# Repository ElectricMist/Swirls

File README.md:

PCBs and Front panels Available at Pusherman at a fair price :
https://pushermanproductions.com/product/swirls-lamb-8hp-tides-sheep-black-fr4-reversible-panel-pcb-set/

Swirls is a 8HP version of Mutable Instruments Tides

- PCB v1.0 is tested and working
  known issues :
  side holes for the trimmers are too small,
  Silkscreen Mistake (C26 & R27 are flipped)
  
- PCB V1.1 
  the errors of v1.0 are fixed
  
The front panel is double Side
  - One side for Swirls (running the Tides firmware)
  - One side for Lamb (running the Sheep firmware)

Please if you are planning to sell some pcbs and panels, contact me first.

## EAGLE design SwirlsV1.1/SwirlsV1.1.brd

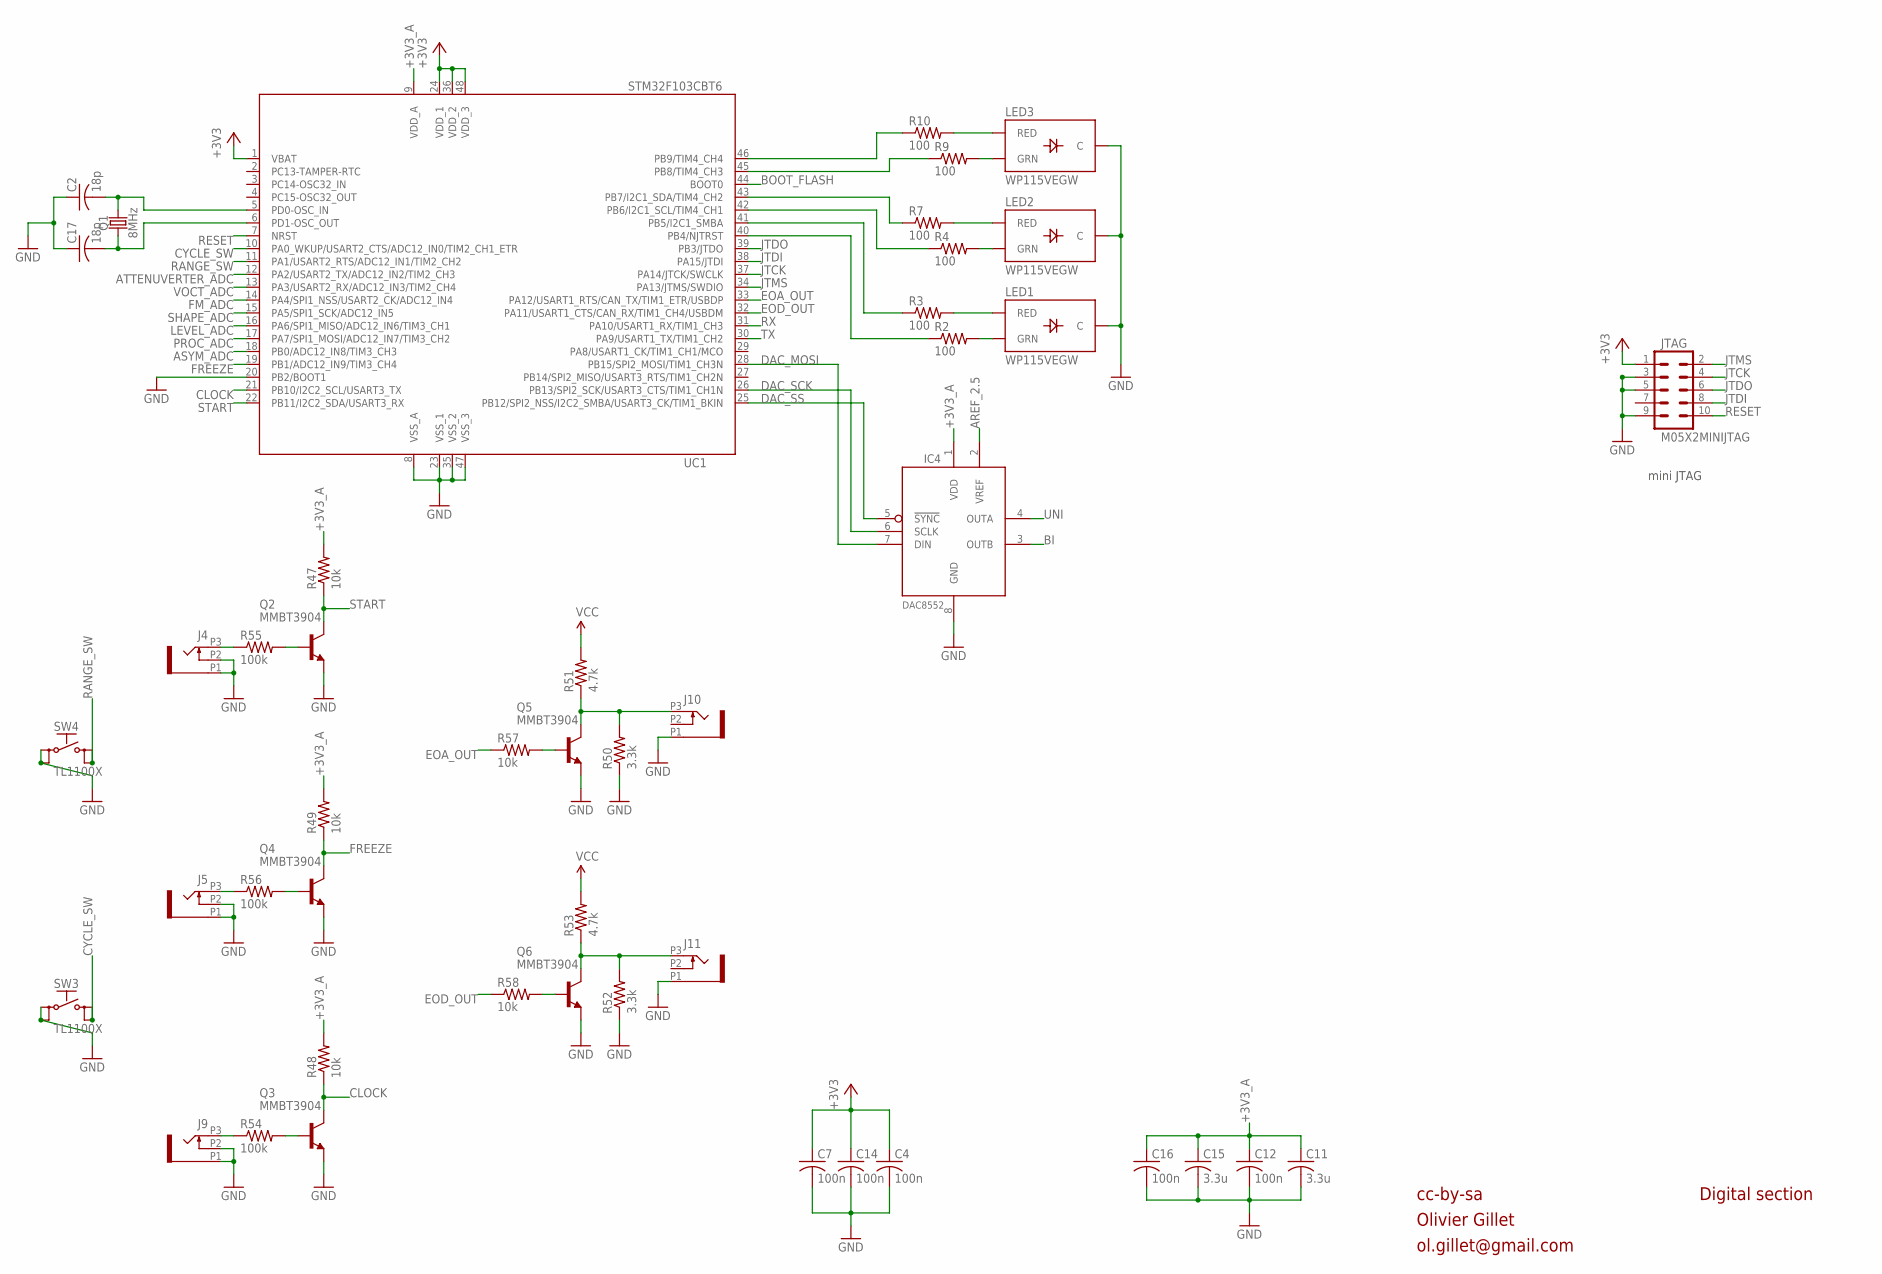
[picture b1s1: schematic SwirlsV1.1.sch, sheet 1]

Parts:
C2, C17: 18p; C0603
C4, C7, C12, C14, C16: 100n; C0603
C11, C15: 3.3u; C0603
IC4: DAC8552; MSOP-8
J4, J5, J9, J10, J11: PJ301_GUI6; OG-PJ301_VARIATIONS_WQP_PJ_301M6
JTAG: M05X2MINIJTAG; 2X5-1.27
LED1, LED2, LED3: WP115VEGW; LED-BICOLOR-THROUGHHOLE
Q1: 8MHz; HC49UP
Q2, Q3, Q4, Q5, Q6: MMBT3904; SOT23-BEC
R2, R3, R4, R7, R9, R10: 100; R0603
R47, R48, R49, R57, R58: 10k; R0603
R50, R52: 3.3k; R0603
R51, R53: 4.7k; R0603
R54, R55, R56: 100k; R0603
SW3, SW4: TL1100X
UC1: STM32F103CBT6; LQFP48

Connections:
+3V3: C4.1, C7.1, C14.1, JTAG.1, UC1.1 (VBAT), UC1.24 (VDD_1), UC1.36 (VDD_2), UC1.48 (VDD_3); also elsewhere on the board
+3V3_A: C11.1, C12.1, C15.1, C16.1, IC4.1 (VDD), R47.2, R48.2, R49.2, UC1.9 (VDD_A); also elsewhere on the board
AREF_2.5: IC4.2 (VREF); also elsewhere on the board
ASYM_ADC: UC1.18 (PB0/ADC12_IN8/TIM3_CH3); also elsewhere on the board
ATTENUVERTER_ADC: UC1.12 (PA2/USART2_TX/ADC12_IN2/TIM2_CH3); also elsewhere on the board
BI: IC4.3 (OUTB); also elsewhere on the board
BOOT_FLASH: UC1.44 (BOOT0)
CLOCK: Q3.C, R48.1, UC1.21 (PB10/I2C2_SCL/USART3_TX)
CYCLE_SW: SW3.3 (S), SW3.4 (S1), UC1.10 (PA0_WKUP/USART2_CTS/ADC12_IN0/TIM2_CH1_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)
DAC_MOSI: IC4.7 (DIN), UC1.28 (PB15/SPI2_MOSI/TIM1_CH3N)
DAC_SCK: IC4.6 (SCLK), UC1.26 (PB13/SPI2_SCK/USART3_CTS/TIM1_CH1N)
DAC_SS: IC4.5 (!SYNC), UC1.25 (PB12/SPI2_NSS/I2C2_SMBA/USART3_CK/TIM1_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)
EOA_OUT: R57.1, UC1.33 (PA12/USART1_RTS/CAN_TX/TIM1_ETR/USBDP)
EOD_OUT: R58.1, UC1.32 (PA11/USART1_CTS/CAN_RX/TIM1_CH4/USBDM)
FM_ADC: UC1.14 (PA4/SPI1_NSS/USART2_CK/ADC12_IN4); also elsewhere on the board
FREEZE: Q4.C, R49.1, UC1.19 (PB1/ADC12_IN9/TIM3_CH4)
GND: C2.1, C4.2, C7.2, C11.2, C12.2, C14.2, C15.2, C16.2, C17.1, IC4.8 (GND), J4.P1 (1), J4.P2 (2), J5.P1 (1), J5.P2 (2), J9.P1 (1), J9.P2 (2), J10.P1 (1), J11.P1 (1), JTAG.3, JTAG.5, JTAG.9, LED1.2 (C), LED2.2 (C), LED3.2 (C), Q2.E, Q3.E, Q4.E, Q5.E, Q6.E, R50.1, R52.1, SW3.1, SW3.2 (P1), SW4.1, SW4.2 (P1), UC1.8 (VSS_A), UC1.20 (PB2/BOOT1), UC1.23 (VSS_1), UC1.35 (VSS_2), UC1.47 (VSS_3); also elsewhere on the board
JTCK: JTAG.4, UC1.37 (PA14/JTCK/SWCLK)
JTDI: JTAG.8, UC1.38 (PA15/JTDI)
JTDO: JTAG.6, UC1.39 (PB3/JTDO)
JTMS: JTAG.2, UC1.34 (PA13/JTMS/SWDIO)
LEVEL_ADC: UC1.16 (PA6/SPI1_MISO/ADC12_IN6/TIM3_CH1); also elsewhere on the board
unnamed: C2.2, Q1.2, UC1.5 (PD0-OSC_IN)
unnamed: C17.2, Q1.1, UC1.6 (PD1-OSC_OUT)
unnamed: J5.P3 (3), R56.1
unnamed: Q4.B, R56.2
unnamed: J9.P3 (3), R54.1
unnamed: Q3.B, R54.2
unnamed: Q6.B, R58.2
unnamed: J11.P3 (3), Q6.C, R52.2, R53.1
unnamed: LED3.3 (RED), R10.2
unnamed: LED3.1 (GRN), R9.2
unnamed: LED2.3 (RED), R7.2
unnamed: LED2.1 (GRN), R4.2
unnamed: LED1.3 (RED), R3.2
unnamed: LED1.1 (GRN), R2.2
unnamed: R10.1, UC1.46 (PB9/TIM4_CH4)
unnamed: R9.1, UC1.45 (PB8/TIM4_CH3)
unnamed: R7.1, UC1.43 (PB7/I2C1_SDA/TIM4_CH2)
unnamed: R4.1, UC1.42 (PB6/I2C1_SCL/TIM4_CH1)
unnamed: R3.1, UC1.41 (PB5/I2C1_SMBA)
unnamed: R2.1, UC1.40 (PB4/NJTRST)
unnamed: J10.P3 (3), Q5.C, R50.2, R51.1
unnamed: Q5.B, R57.2
unnamed: J4.P3 (3), R55.1
unnamed: Q2.B, R55.2
PROC_ADC: UC1.17 (PA7/SPI1_MOSI/ADC12_IN7/TIM3_CH2); also elsewhere on the board
RANGE_SW: SW4.3 (S), SW4.4 (S1), UC1.11 (PA1/USART2_RTS/ADC12_IN1/TIM2_CH2)
RESET: JTAG.10, UC1.7 (NRST)
RX: UC1.31 (PA10/USART1_RX/TIM1_CH3)
SHAPE_ADC: UC1.15 (PA5/SPI1_SCK/ADC12_IN5); also elsewhere on the board
START: Q2.C, R47.1, UC1.22 (PB11/I2C2_SDA/USART3_RX)
TX: UC1.30 (PA9/USART1_TX/TIM1_CH2)
UNI: IC4.4 (OUTA); also elsewhere on the board
VCC: R51.2, R53.2; also elsewhere on the board
VOCT_ADC: UC1.13 (PA3/USART2_RX/ADC12_IN3/TIM2_CH4); also elsewhere on the board

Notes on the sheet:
cc-by-sa
Olivier Gillet
ol.gillet@gmail.com
Digital section
mini JTAG

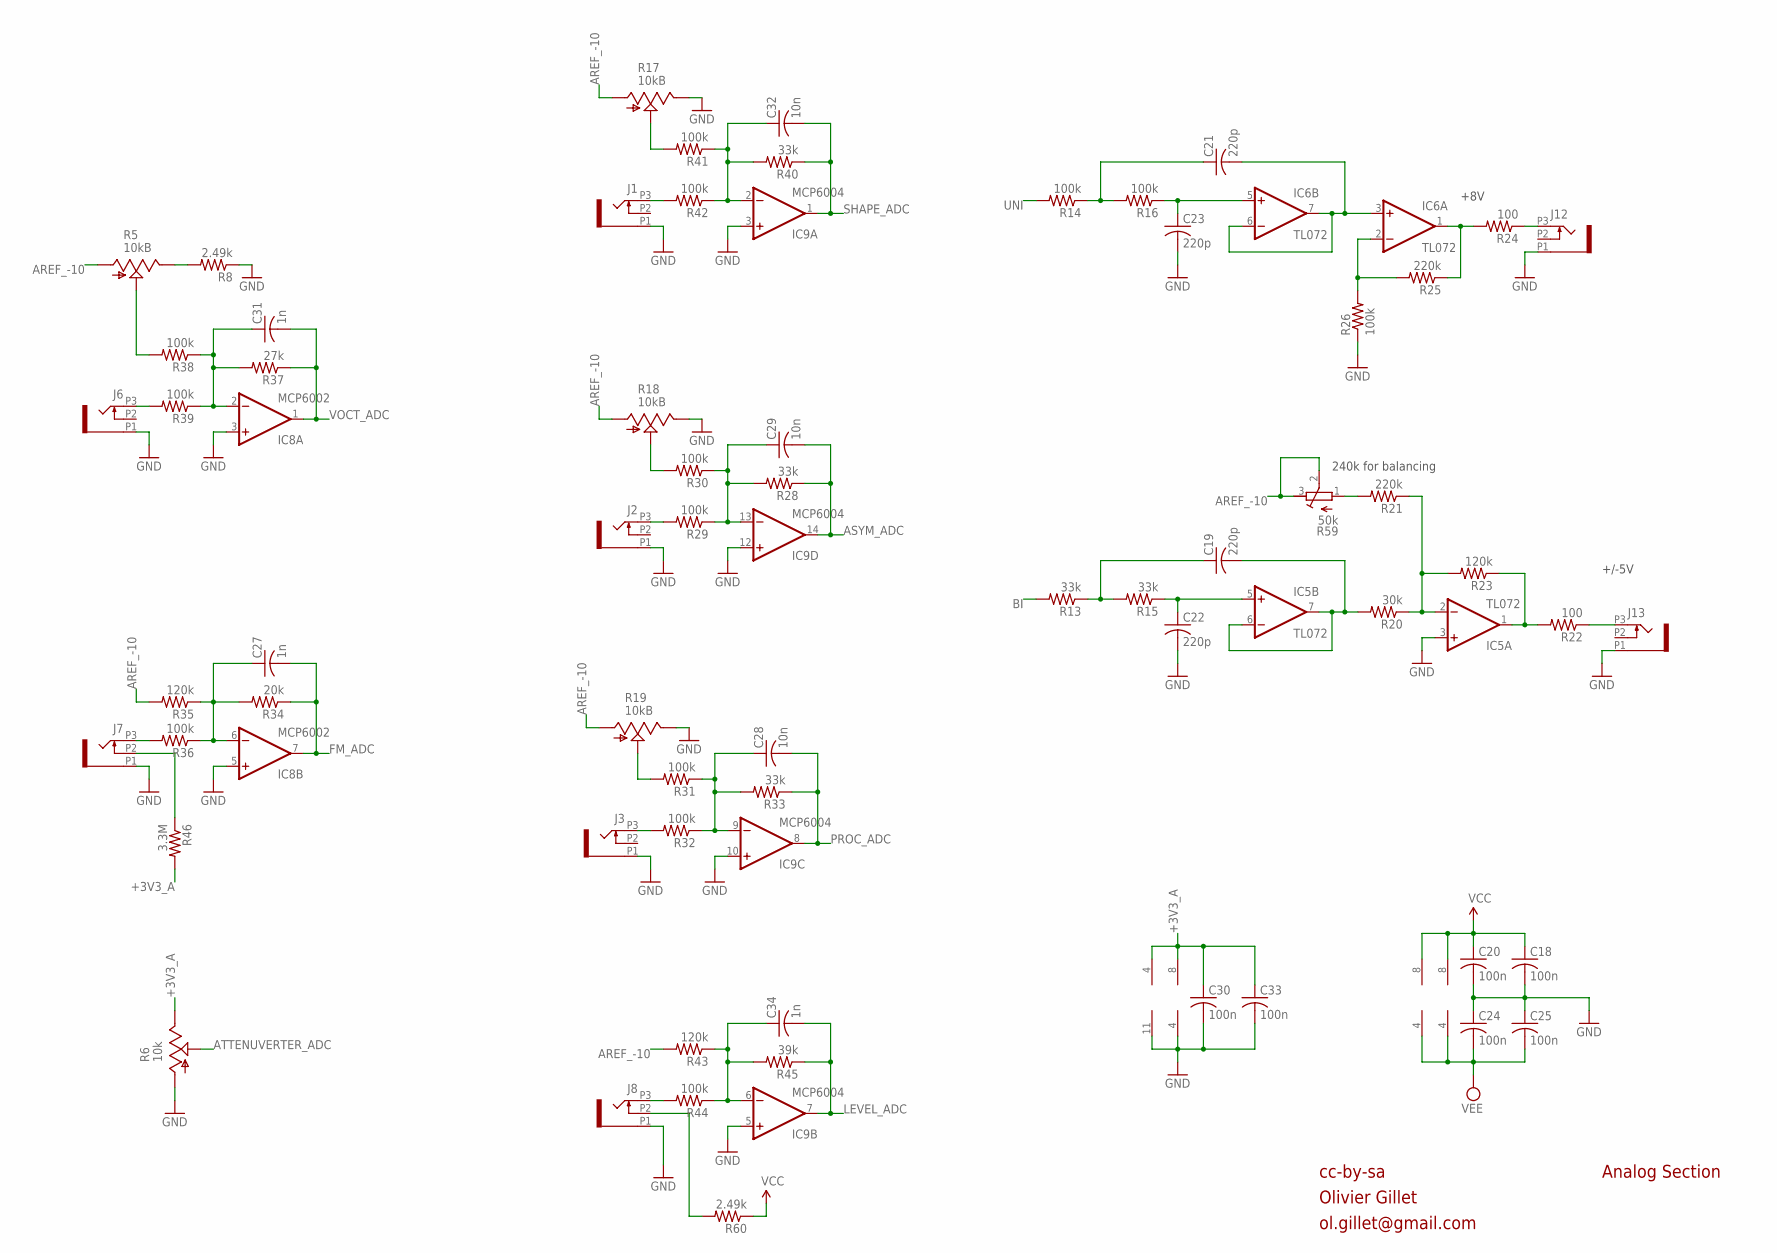
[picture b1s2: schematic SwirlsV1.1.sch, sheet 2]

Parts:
C18, C20, C24, C25, C30, C33: 100n; C0603
C19, C21, C22, C23: 220p; C0603
C27, C31, C34: 1n; C0603
C28, C29, C32: 10n; C0603
IC5, IC6: TL072; TSSOP-8
IC8: MCP6002; SO08
IC9: MCP6004; TSSOP14
J1, J2, J3, J6, J7, J8, J12, J13: PJ301_GUI6; OG-PJ301_VARIATIONS_WQP_PJ_301M6
R5: 10kB; ALPS_POT_VERTICAL_PS
R6: 10k; TALLTRIMMER
R8: 2.49k; R0603
R13, R15, R28, R33, R40: 33k; R0603
R14, R16, R26, R29, R30, R31, R32, R36, R38, R39, R41, R42, R44: 100k; R0603
R17, R18, R19: 10kB; TALLTRIMMER
R20: 30k; R0603
R21, R25: 220k; R0603
R22, R24: 100; R0603
R23, R35, R43: 120k; R0603
R34: 20k; R0603
R37: 27k; R0603
R45: 39k; R0603
R46: 3.3M; R0603
R59: 50k; RTRIM3296W
R60: 2.49k; R0805

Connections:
+3V3_A: C30.1, C33.1, IC8.8 (V+), IC9.4 (V+), R6.P$1 (E), R46.2; also elsewhere on the board
AREF_-10: R5.P$3 (A), R17.P$3 (A), R18.P$3 (A), R19.P$3 (A), R35.2, R43.2, R59.2 (S), R59.3 (E); also elsewhere on the board
ASYM_ADC: C29.2, IC9.14 (OUT), R28.1; also elsewhere on the board
ATTENUVERTER_ADC: R6.P$2 (S); also elsewhere on the board
BI: R13.2; also elsewhere on the board
BI_OUT: IC5.1 (OUT), R22.2, R23.1
FM_ADC: C27.2, IC8.7 (OUT), R34.1; also elsewhere on the board
F_CV: IC5.2 (-IN), R20.1, R21.1, R23.2
GND: C18.2, C20.2, C22.2, C23.2, C24.1, C25.1, C30.2, C33.2, IC5.3 (+IN), IC8.3 (+IN), IC8.4 (V-), IC8.5 (+IN), IC9.3 (+IN), IC9.5 (+IN), IC9.10 (+IN), IC9.11 (V-), IC9.12 (+IN), J1.P1 (1), J2.P1 (1), J3.P1 (1), J6.P1 (1), J7.P1 (1), J8.P1 (1), J12.P1 (1), J13.P1 (1), R6.P$3 (A), R8.1, R17.P$1 (E), R18.P$1 (E), R19.P$1 (E), R26.1; also elsewhere on the board
LEVEL_ADC: C34.2, IC9.7 (OUT), R45.1; also elsewhere on the board
unnamed: J1.P3 (3), R42.2
unnamed: C32.1, IC9.2 (-IN), R40.2, R41.1, R42.1
unnamed: R17.P$2 (S), R41.2
unnamed: J2.P3 (3), R29.2
unnamed: C29.1, IC9.13 (-IN), R28.2, R29.1, R30.1
unnamed: J7.P2 (2), R46.1
unnamed: R18.P$2 (S), R30.2
unnamed: J3.P3 (3), R32.2
unnamed: C28.1, IC9.9 (-IN), R31.1, R32.1, R33.2
unnamed: R19.P$2 (S), R31.2
unnamed: J8.P3 (3), R44.2
unnamed: C34.1, IC9.6 (-IN), R43.1, R44.1, R45.2
unnamed: J6.P3 (3), R39.2
unnamed: C31.1, IC8.2 (-IN), R37.2, R38.1, R39.1
unnamed: R5.P$2 (S), R38.2
unnamed: J13.P3 (3), R22.1
unnamed: R5.P$1 (E), R8.2
unnamed: J7.P3 (3), R36.2
unnamed: C27.1, IC8.6 (-IN), R34.2, R35.1, R36.1
unnamed: R21.2, R59.1 (A)
unnamed: IC6.2 (-IN), R25.2, R26.2
unnamed: C19.2, IC5.6 (-IN), IC5.7 (OUT), R20.2
unnamed: C22.1, IC5.5 (+IN), R15.1
unnamed: C19.1, R13.1, R15.2
unnamed: IC6.1 (OUT), R24.2, R25.1
unnamed: J8.P2 (2), R60.2
unnamed: C21.2, IC6.3 (+IN), IC6.6 (-IN), IC6.7 (OUT)
unnamed: C23.1, IC6.5 (+IN), R16.1
unnamed: C21.1, R14.1, R16.2
PROC_ADC: C28.2, IC9.8 (OUT), R33.1; also elsewhere on the board
SHAPE_ADC: C32.2, IC9.1 (OUT), R40.1; also elsewhere on the board
UNI: R14.2; also elsewhere on the board
UNI_OUT: J12.P3 (3), R24.1
VCC: C18.1, C20.1, IC5.8 (V+), IC6.8 (V+), R60.1; also elsewhere on the board
VEE: C24.2, C25.2, IC5.4 (V-), IC6.4 (V-); also elsewhere on the board
VOCT_ADC: C31.2, IC8.1 (OUT), R37.1; also elsewhere on the board

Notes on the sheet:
cc-by-sa
Olivier Gillet
ol.gillet@gmail.com
Analog Section
+8V
+/-5V
240k for balancing

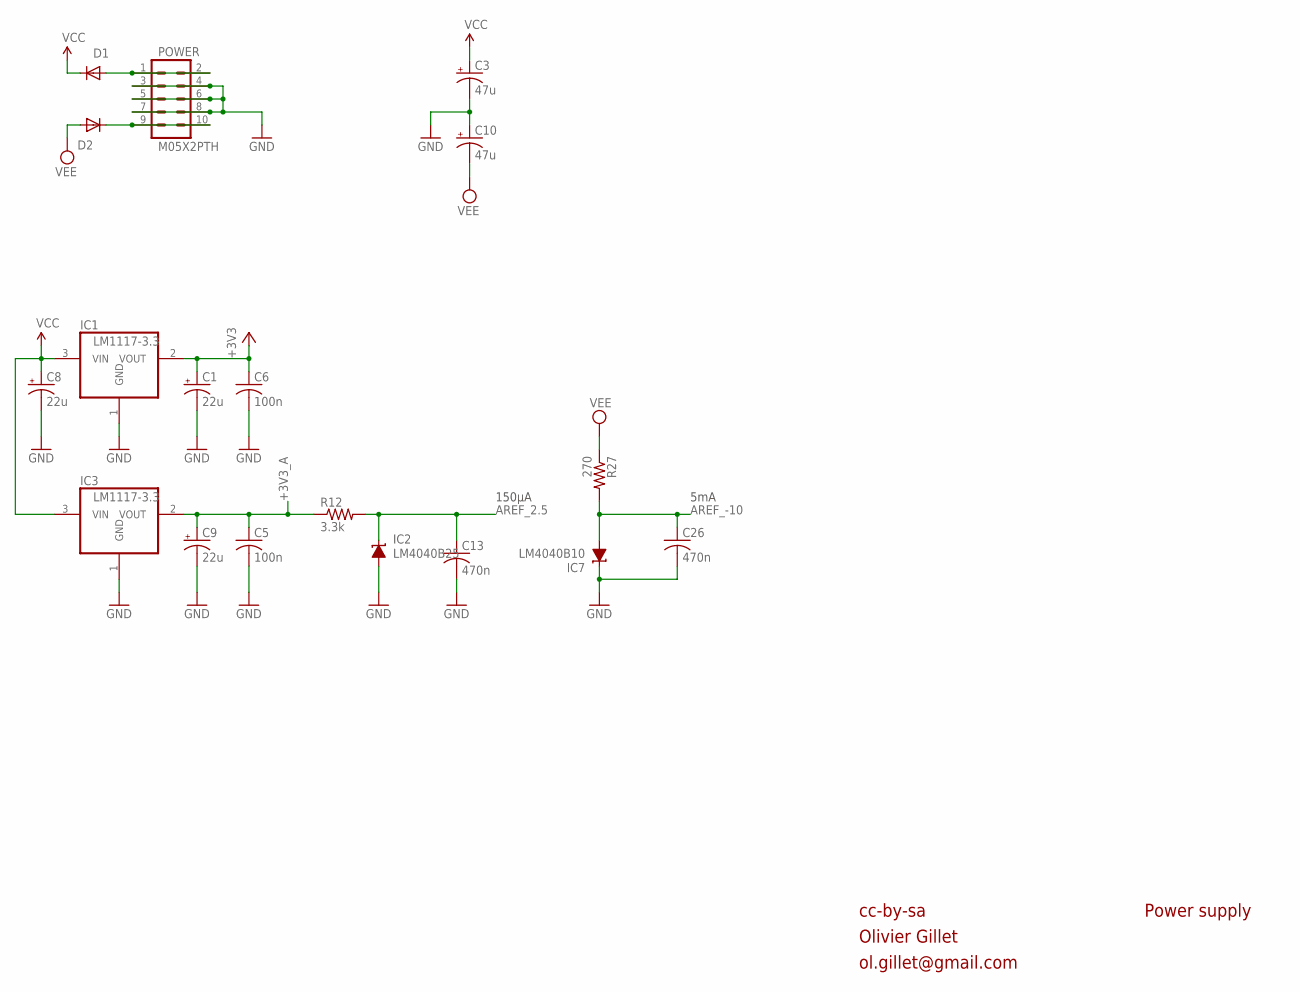
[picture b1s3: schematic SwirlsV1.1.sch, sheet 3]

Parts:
C1, C8, C9: 22u; PANASONIC_C
C3, C10: 47u; PANASONIC_D
C5, C6: 100n; C0603
C13, C26: 470n; C0603
D1, D2: 1N5819HW; SOD123
IC1, IC3: LM1117-3.3; SOT223
IC2: LM4040B25; DBZ_R-PDSO-G3
IC7: LM4040B10; DBZ_R-PDSO-G3
POWER: M05X2PTH; AVR_ICSP
R12: 3.3k; R0603
R27: 270; R0603

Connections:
+3V3: C1.+, C6.1, IC1.2 (VOUT); also elsewhere on the board
+3V3_A: C5.1, C9.+, IC3.2 (VOUT), R12.1; also elsewhere on the board
AREF_2.5: C13.1, IC2.1 (C), R12.2; also elsewhere on the board
AREF_-10: C26.1, IC7.2 (A), R27.2; also elsewhere on the board
GND: C1.-, C3.-, C5.2, C6.2, C8.-, C9.-, C10.+, C13.2, C26.2, IC1.1 (GND), IC2.2 (A), IC3.1 (GND), IC7.1 (C), POWER.3, POWER.4, POWER.5, POWER.6, POWER.7, POWER.8; also elsewhere on the board
unnamed: D1.A, POWER.1, POWER.2
unnamed: D2.C, POWER.9, POWER.10
VCC: C3.+, C8.+, D1.C, IC1.3 (VIN), IC3.3 (VIN); also elsewhere on the board
VEE: C10.-, D2.A, R27.1; also elsewhere on the board

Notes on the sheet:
cc-by-sa
Olivier Gillet
ol.gillet@gmail.com
Power supply
5mA
150µA

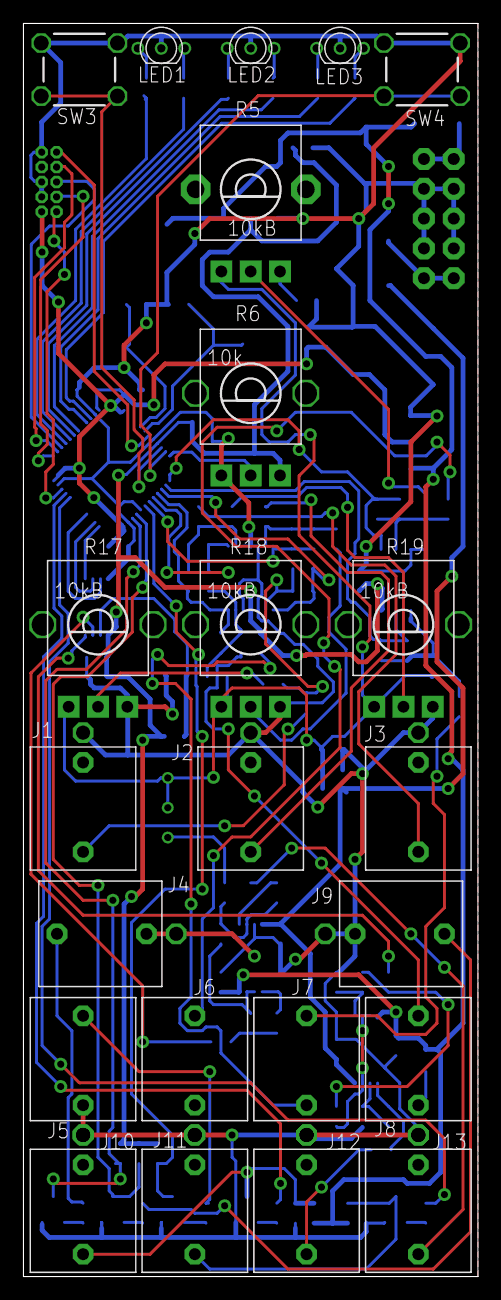
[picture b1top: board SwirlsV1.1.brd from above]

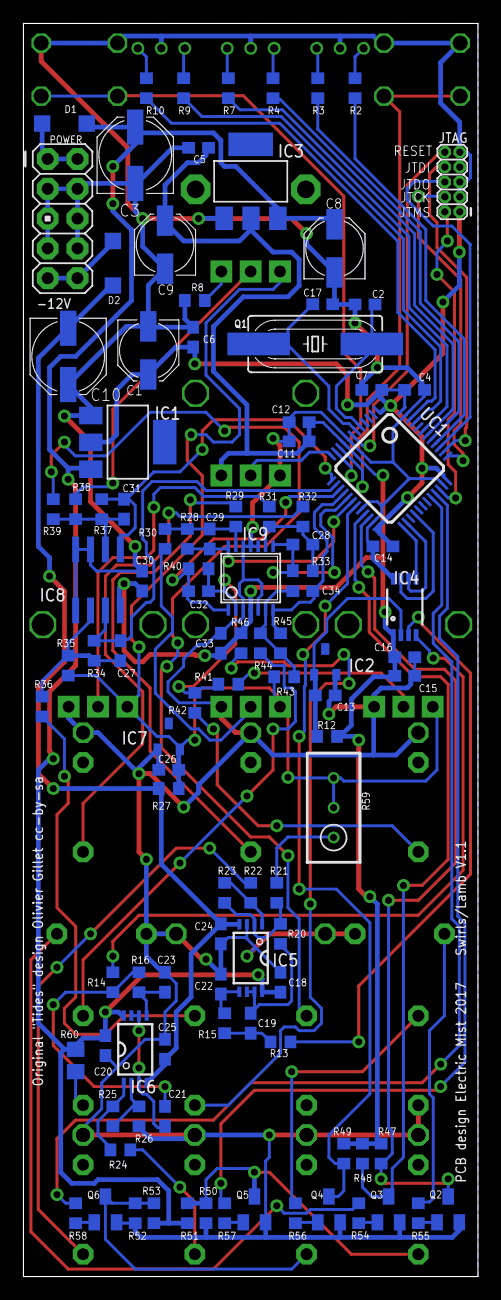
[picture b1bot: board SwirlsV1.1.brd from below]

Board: 2 copper layers, 38.7 x 106.8 mm, 130 parts (107 on the bottom side), 89 nets.

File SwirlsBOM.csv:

SWIRLS V1.0,,,,,,,
Index,Qty,Description,Specs,Value,Package,Ref. Mouser,References
SMT parts,,,,,,,
"R2, R3, R4, R7, R9, R10, R22, R24",8,"Resistor, 1%",,100,0603,652-CR0603FX-1000ELF,
R27,1,"Resistor, 1%",,270,0603,652-CR0603FX-2700ELF,
R8,1,"Resistor, 1%",,2.49k,0603,652-CR0603FX-2491ELF,
R60,1,"Resistor, 1%",,2.49k,0805,652-CR0805FX-2491ELF,
"R12, R50, R52",3,"Resistor, 1%",,3.3k,0603,652-CR0603-FX3301ELF,
"R51, R53",2,"Resistor, 1%",,4.7k,0603,652-CR0603FX-4701ELF,
"R47, R48, R49, R57, R58",5,"Resistor, 1%",,10k,0603,652-CR0603-FX-1002GLF,
R34,1,"Resistor, 1%",,20k,0603,652-CR0603FX-2002ELF,
R37,1,"Resistor, 1%",,27k,0603,652-CR0603FX-2702ELF,
R20,1,"Resistor, 1%",,30k,0603,652-CR0603FX-3002ELF,
"R13, R15, R28, R33, R40",5,"Resistor, 1%",,33k,0603,652-CR0603FX-3302ELF,
R45,1,"Resistor, 1%",,39k,0603,652-CR0603FX-3902ELF,
"R14, R16, R26, R29, R30, R31, R32, R36, R38, R39, R41, R42, R44, R54, R55, R56",16,"Resistor, 1%",,100k,0603,652-CR0603-FX-1003GLF,
"R23, R35, R43",3,"Resistor, 1%",,120k,0603,652-CR0603FX-1203ELF,
"R21, R25",2,"Resistor, 1%",,220k,0603,652-CR0603FX-2203ELF,
R46,1,"Resistor, 1%",,3.3M,0603,71-CRCW06033M30FKEA,
"C2, C17",2,"Capacitor, ceramic",,18p,0603,81-GRM185C1H180JA01J,
"C19, C21, C22, C23",4,"Capacitor, ceramic",">= 16V, <= 2%, C0G",220p,0603,81-GRM185C1H221GA01D,
"C27, C31, C34",3,"Capacitor, ceramic",">= 50V, <= 2%, C0G",1n,0603,81-GRM1885C1H102FA1J,
"C28, C29, C32",3,"Capacitor, ceramic",">= 50V, <= 5%",10n,0603,81-GRM18R71H103JA01D,
"C4, C5, C6, C7, C12, C14, C16, C18, C20, C24, C25, C30, C33",13,"Capacitor, ceramic",>= 16V,100n,0603,81-GRM188R71E104JA1J,
"C13, C26",2,"Capacitor, ceramic",>= 16V,470n,0603,81-GRM18F51C474ZA01J,
"C11, C15",2,"Capacitor, ceramic",>= 6.3V,3.3u,0603,81-GRM188R61A335KE5D,
"C1, C8, C9",3,"Capacitor, electrolytic",>= 25V,22u,Panasonic C,667-EEE-FP1E220AR,EEE-FP1E220AR
"C3, C10",2,"Capacitor, electrolytic",>= 25V,47u,Panasonic D,667-EEE-FK1V470P,EEEFK1V470P
"D1, D2",2,1N5819HW diode,,,SOD123,621-1N5819HW-F,Diodes Inc 1N5819HW-7-F
"IC1, IC3",2,LM1117-3.3V LDO Vreg,,3.3V,SO223,926-LM1117MPX3.3NOPB,National LM1117MPX3.3NOPB
IC2,1,LM4040 Shunt Vref,"A, B or C grade",2.5V,SOT23,595-LM4040C25IDBZR,Texas Instruments LM4040C25IDBZ
IC7,1,LM4040 Shunt Vref,"A, B or C grade",10V,SOT23,595-LM4040C10IDBZR,Texas Instruments LM4040C10IDBZ
IC4,1,DAC8552 dual 16-bit DAC,,,MSOP8,595-DAC8552IDGKT,Texas Instruments DAC8552IDGKT
"IC5, IC6",2,TL072 dual op-amp,,,TSSOP-8,595-TL072CPWR,TI TL072CPWR
IC8,1,MCP6002 dual op-amp R2R IO,,,SOIC8,579-MCP6002-I/SN,MCP6002-I/SN
IC9,1,MCP6004 dual op-amp R2R IO,,,TSSOP-14,579-MCP6004-I/ST,MCP6004-I/ST
"Q2, Q3, Q4, Q5, Q6",5,NPN transistor MMBT3904,,,SOT23,863-MMBT3904LT1G,On Semi MMBT3904LT1G
Q1,1,8 MHz quartz,,,HC49,815-ABLS2-8-D4Y-T,Abracon ABLS2-8.000MHZ-D4Y-T
UC1,1,STM32F103CBT6 MCU,,,LQFP48,511-STM32F103CBT6,ST STM32F103CBT6
TH parts,,MFG Part No:D6R90 F1 LFS,,,,,
"J1, J2, J3, J4, J5, J6, J7, J8, J9, J10, J11, J12, J13",13,Vertical jack connector,,,,,PJ-301-M-12
"LED1, LED2, LED3",3,"LED, Red/Green, 3 terminals, common K",,,3 terminals,604-WP115VEGW,Kingbright WP115VEGW
"SW3, SW4",2,Push-button 6.0X2.8MM,,,,612-TL1105SP-250,E-switch TL1105SPF250Q
,2,Push-button caps,,,,612-1R-BK,E-switch 1RBLK
R5,1,"10k linear pot, 15mm shaft",,,,,https://www.thonk.co.uk/shop/alpha-9mm-pots/
"R6, R17, R18, R19",4,10k linear Tall Trimmer,,,,,https://www.thonk.co.uk/shop/ttpots/
R59,1,"50k Trimmer resistor, 25 turns, top adjust.",,50k,,652-3296W-1-503LF,3296W-1-503LF
JP1,1,"2x5 male header, 2.54mm pitch",,,,649-67996-410HLF,
JP2,1,"2x5, 1.27mm pitch male header",,,,649-221111-00010T4LF,

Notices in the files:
SwirlsV1.1/SwirlsV1.1.brd:
Original "Tides" design Olivier Gillet cc-by-sa
parts and their libraries:
switch-e-switch: Copyright (C) 2010, Bob Starr
SparkFun-Clocks: Licensing: Creative Commons ShareAlike 4.0 International - https://creativecommons.org/licenses/by-sa/4.0
